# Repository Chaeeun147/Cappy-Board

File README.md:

# Cappy-Board
This is a project I made through a Stasis Hackclub Starter Project Tutorial. It is a Blinky Board, the first PCB I ever made!
When the PCB is turned on, the LEDs will start to blink!

I made this project because I wanted to start learning hardware, and I thought the Blinky Board in the starter projects would be a great place to start. The guide seemed simple enough, and it would be a great starter project. I also always wanted to try to make my own PCB, but never got a chance. I finally got a chance through this project!!

BOM:
| Pert Name | Quantity | Description | Cost | Distrubutor | Link |
| --------- | -------- | ----------- | ---- | ------------| - |
| Custom PCB | 5 | PCB | $2.00 | JLCPCB | https://jlcpcb.com/ |

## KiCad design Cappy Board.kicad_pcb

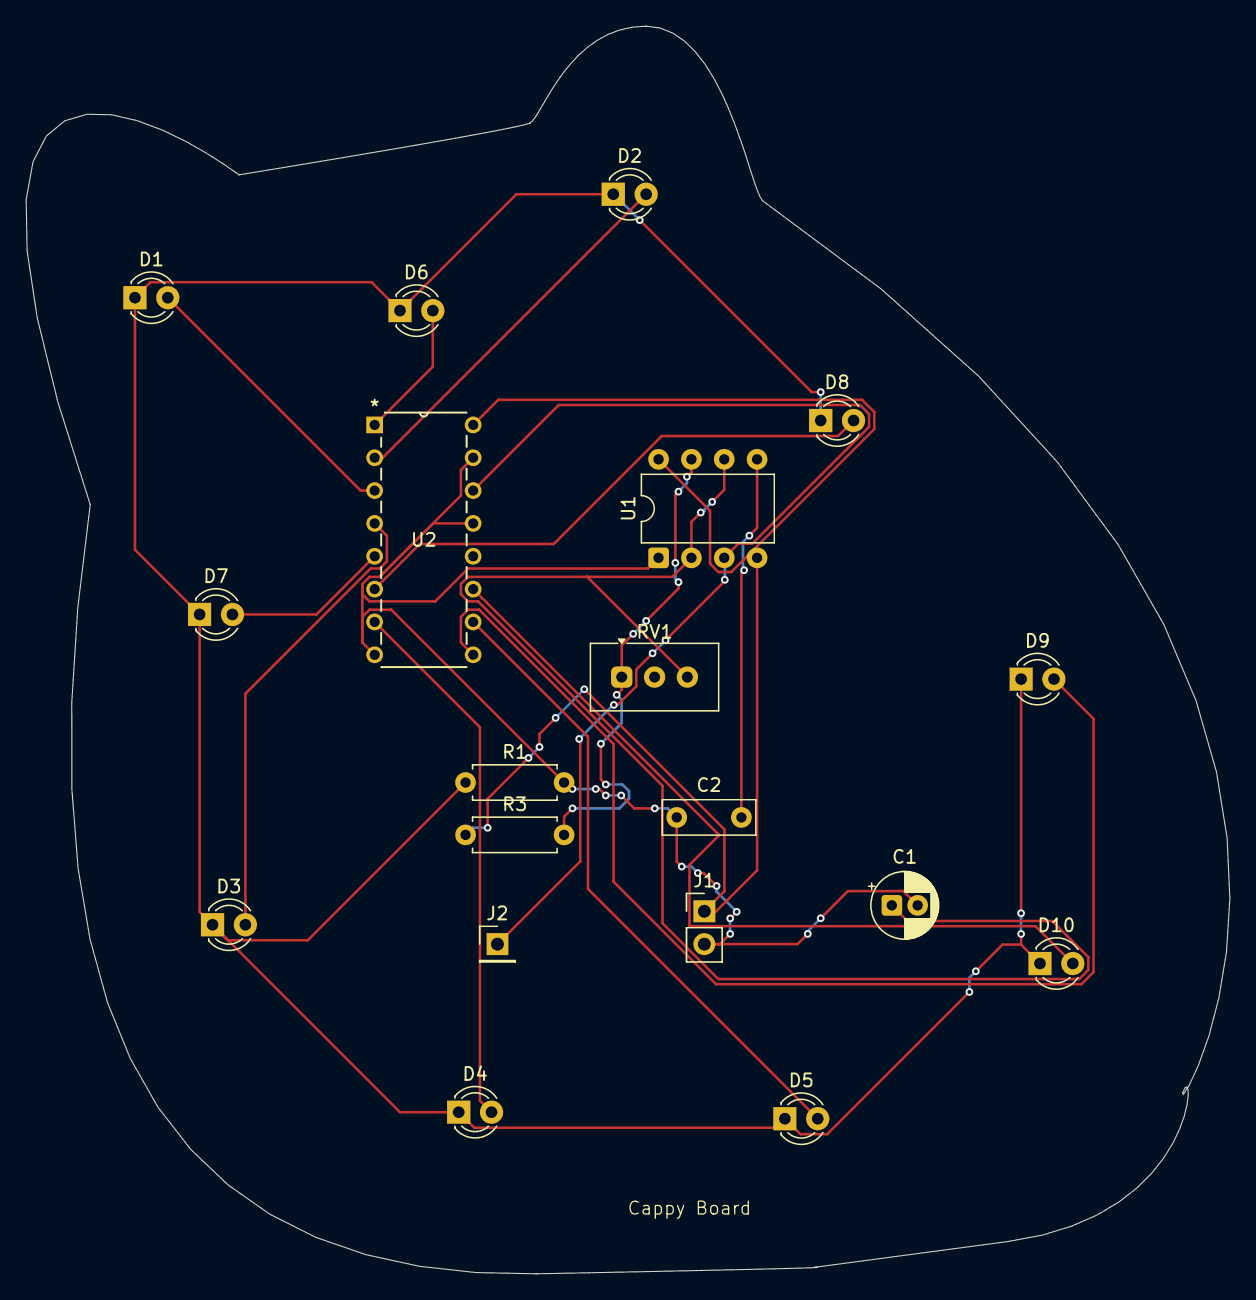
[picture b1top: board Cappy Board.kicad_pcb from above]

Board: 2 copper layers, 93.1 x 96.5 mm, 19 parts (0 on the bottom side), 17 nets.

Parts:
C1: 1 µF; CP_Radial_D5.0mm_P2.00mm
C2: 0.01 µF; C_Disc_D7.0mm_W2.5mm_P5.00mm
D1, D2, D3, D4, D5, D6, D7, D8, D9, D10: LED; LED_D3.0mm
J1: Conn_01x02_Socket; PinHeader_1x02_P2.54mm_Vertical
J2: Conn_01x01_Socket; PinHeader_1x01_P2.54mm_Vertical
R1: 470; R_Axial_DIN0207_L6.3mm_D2.5mm_P7.62mm_Horizontal
R3: 1k; R_Axial_DIN0207_L6.3mm_D2.5mm_P7.62mm_Horizontal
RV1: 50k; Potentiometer_Vishay_T93YA_Vertical
U1: NE555P; DIP-8_W7.62mm
U2: 4017; N16

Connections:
+5V: J1.1, R3.1, U1.4 (~RST), U1.8 (VCC), U2.16 (VDD)
/<NO NET>: J2.1 (Pin_1_1), U1.3 (OUT), U2.14 (CLK)
/TR: C1.1, RV1.3, U1.2 (TRIG), U1.6 (THRES)
GND: C1.2, C2.1, J1.2, R1.2, U1.1 (GND), U2.8 (VSS), U2.13 (CKEN), U2.15 (Reset)
unnamed: D1.2 (A), U2.3 (Q0)
unnamed: D1.1 (K), D2.1 (K), D3.1 (K), D4.1 (K), D5.1 (K), D6.1 (K), D7.1 (K), D8.1 (K), D9.1 (K), D10.1 (K), R1.1
unnamed: D2.2 (A), U2.2 (Q1)
unnamed: D3.2 (A), U2.4 (Q2)
unnamed: D4.2 (A), U2.7 (Q3)
unnamed: D5.2 (A), U2.10 (Q4)
unnamed: D6.2 (A), U2.1 (Q5)
unnamed: D7.2 (A), U2.5 (Q6)
unnamed: D8.2 (A), U2.6 (Q7)
unnamed: D9.2 (A), U2.9 (Q8)
unnamed: D10.2 (A), U2.11 (Q9)
unnamed: C2.2, U1.5 (CONT)
unnamed: R3.2, RV1.1, U1.7 (DISCH)

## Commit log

2026-04-15 Enhance README with project details and images
    Expanded project description and added images.
2026-04-15 Refine project description in README.md
    Removed redundant phrasing to improve clarity.
2026-04-22 Add table to README.md
2026-04-22 Revise table structure in README.md
    Updated table format and added a new row for Custom PCB.
2026-04-22 Fix table formatting in README.md
2026-04-22 Update quantity and cost for Custom PCB in README
2026-04-22 Update BOM table to include distributor information
2026-04-22 Add 'Link' column to BOM in README
2026-06-24 Update README with project image and description
    Added an image and introductory text to the README.
